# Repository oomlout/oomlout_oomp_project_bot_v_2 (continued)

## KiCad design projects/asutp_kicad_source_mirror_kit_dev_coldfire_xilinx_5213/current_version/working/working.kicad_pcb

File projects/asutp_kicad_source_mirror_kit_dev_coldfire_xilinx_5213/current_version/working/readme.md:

# kicad_source_mirror
 
## summary 
* id: asutp_kicad_source_mirror_kit_dev_coldfire_xilinx_5213
* user: asutp
* name: kicad_source_mirror
* board: kit_dev_coldfire_xilinx_5213
* repo: https://github.com/asutp/kicad-source-mirror
* src_file_repo_kicad_pcb: demos/kit-dev-coldfire-xilinx_5213/kit-dev-coldfire-xilinx_5213.kicad_pcb
* src_file_repo_kicad_pcb_link: https://github.com/asutp/kicad-source-mirror/tree/master/demos/kit-dev-coldfire-xilinx_5213/kit-dev-coldfire-xilinx_5213.kicad_pcb

* src_file_repo_sch: demos/interf_u/interf_u.sch
* src_file_repo_sch_link: https://github.com/asutp/kicad-source-mirror/tree/master/demos/interf_u/interf_u.sch
* full details link: https://github.com/oomlout/oomlout_oomp_project_bot_v_2/tree/main/projects/asutp_kicad_source_mirror_kit_dev_coldfire_xilinx_5213/current_version/working  

## pcb  

[board (pdf)](working.pdf)  

## working_bom
| Id | Designator | Footprint | Quantity | Designation | Supplier and ref |  | None | 
| --- | --- | --- | --- | --- | --- | --- | --- | 
| 1 | ABRT_SW1,RST_SW1,SW1,SW2 | SW_PUSH_SMALL | 4 | SW_PUSH |  |  | [''] | 
| 2 | ALLPST1,CLKOUT1,GND1,RS1,TA-1,VREF1 | PINTST | 6 | CONN_1 |  |  | [''] | 
| 3 | BDM_EN1,CAN_TERM1,CLK0,CLK1,CT1,LED_EN1,VDDA1,VX_EN1 | PIN_ARRAY_2X1 | 8 | JUMPER |  |  | [''] | 
| 4 | BDM_PORT1 | pin_array_13x2 | 1 | CONN_13X2 |  |  | [''] | 
| 5 | C1,C2 | SM0805 | 2 | 10pF |  |  | [''] | 
| 6 | C3,C20 | SM0805 | 2 | 1nF |  |  | [''] | 
| 7 | C4,C5,C7,C8,C9,C10,C14,C15,C18,C21,C22,C23,C24,C25,C26,C27,C28,C30,C31,C32,C33,C34,C35,C36,C41,C43,C44,C45,C46,C6,C11,C12,C51,C52,C53,C54,C55,C56,C57,C58,C59,C60,C61 | SM0805 | 43 | 100nF |  |  | [''] | 
| 8 | C16 | SM1206POL | 1 | 10uF |  |  | [''] | 
| 9 | C17 | SM1206POL | 1 | 100uF |  |  | [''] | 
| 10 | C38 | C2V8 | 1 | 10uF |  |  | [''] | 
| 11 | C40 | C2V8 | 1 | 220uF |  |  | [''] | 
| 12 | CAN_EN1,P3 | PIN_ARRAY_2X2 | 2 | CONN_2X2 |  |  | [''] | 
| 13 | COM_SEL1,COM_SEL2,COM_SEL3 | PIN_ARRAY_3X1 | 3 | CONN_3 |  |  | [''] | 
| 14 | D1,D3 | ST23AK#1 | 2 | BAT54 |  |  | [''] | 
| 15 | D7 | D5 | 1 | 1N4004 |  |  | [''] | 
| 16 | D8,D9,LED1,LED2,LED3,LED4,LED5 | SM1206POL | 7 | LED |  |  | [''] | 
| 17 | F1 | FSUPCMS | 1 | FUSE |  |  | [''] | 
| 18 | FB1 | SM1206 | 1 | BEAD |  |  | [''] | 
| 19 | J1 | JACK_ALIM | 1 | JACK_2P |  |  | [''] | 
| 20 | L1,L2 | SM1206 | 2 | 10uH |  |  | [''] | 
| 21 | LEDABRT1 | SM1206POL | 1 | RED |  |  | [''] | 
| 22 | LV1 | TO92-INVERT | 1 | DS1818 |  |  | [''] | 
| 23 | MCU_PORT1 | PIN_ARRAY_30X2 | 1 | CONN_30X2 |  |  | [''] | 
| 24 | P1 | PIN_ARRAY-6X1 | 1 | CONN_6 |  |  | [''] | 
| 25 | P4 | PIN_ARRAY_20X2 | 1 | CONN_20X2 |  |  | [''] | 
| 26 | PULUPEN1,UART_EN0,UART_EN1,UART_EN2 | pin_array_4x2 | 4 | CONN_4X2 |  |  | [''] | 
| 27 | Q1 | SOT23EBC | 1 | 3906 |  |  | [''] | 
| 28 | R1 | SM0805 | 1 | 1M |  |  | [''] | 
| 29 | R2,R15,R16,R17,R18,R19,R20,R21,R25,R45,R47,R48,R49,R50 | SM0805 | 14 | 4,7K |  |  | [''] | 
| 30 | R4,R5,R6,R8,R10,R11,R13,R23,R26,R30,R34,R35 | SM0805 | 12 | 10K |  |  | [''] | 
| 31 | R7,R36,R62,R63 | SM0805 | 4 | 1K |  |  | [''] | 
| 32 | R9 | SM0805 | 1 | 0 |  |  | [''] | 
| 33 | R12 | SM0805 | 1 | 20K |  |  | [''] | 
| 34 | R14,R22,R28,R31,R32,R33,R53 | SM0805 | 7 | 270 |  |  | [''] | 
| 35 | R38 | SM0805 | 1 | 62 |  |  | [''] | 
| 36 | R46 | SM0805 | 1 | 22 |  |  | [''] | 
| 37 | R57 | SM0805 | 1 | 4K7 |  |  | [''] | 
| 38 | R64 | R4 | 1 | 3,3 |  |  | [''] | 
| 39 | RCAN1,RCAN2 | SM0805 | 2 | R |  |  | [''] | 
| 40 | RED1 | SM1206POL | 1 | LED_RESET1 |  |  | [''] | 
| 41 | SW_ONOFF1 | SW_SPDT | 1 | SWITCH_INV |  |  | [''] | 
| 42 | TB1 | bornier2 | 1 | CONN_2 |  |  | [''] | 
| 43 | U1 | VQFP100 | 1 | MCF5213-LQFP100 |  |  | [''] | 
| 44 | U2 | SOT353 | 1 | 74AHC1G14 |  |  | [''] | 
| 45 | U3,U5,U8 | SO16E | 3 | MAX202 |  |  | [''] | 
| 46 | U4 | SO14E | 1 | 74HC125 |  |  | [''] | 
| 47 | U7 | SO8E | 1 | PCA82C251 |  |  | [''] | 
| 48 | U9 | TQFP144 | 1 | XCR3256-TQ144 |  |  | [''] | 
| 49 | UARTCAN0,UARTCAN1,UARTCAN2 | DB9FC | 3 | DB9 |  |  | [''] | 
| 50 | VR1 | DPAK5 | 1 | LT1129_QPACK |  |  | [''] | 
| 51 | Y1 | HC-18UH | 1 | 8MHz |  |  | [''] |

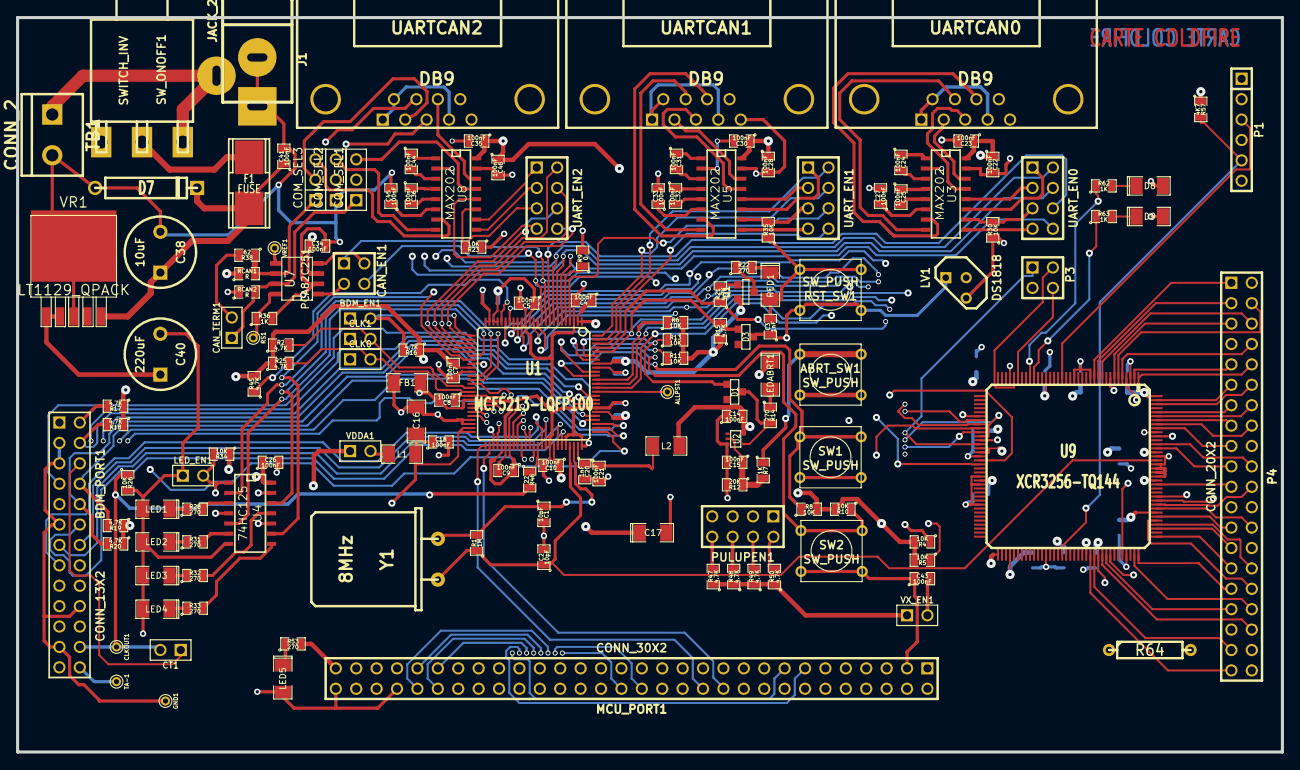
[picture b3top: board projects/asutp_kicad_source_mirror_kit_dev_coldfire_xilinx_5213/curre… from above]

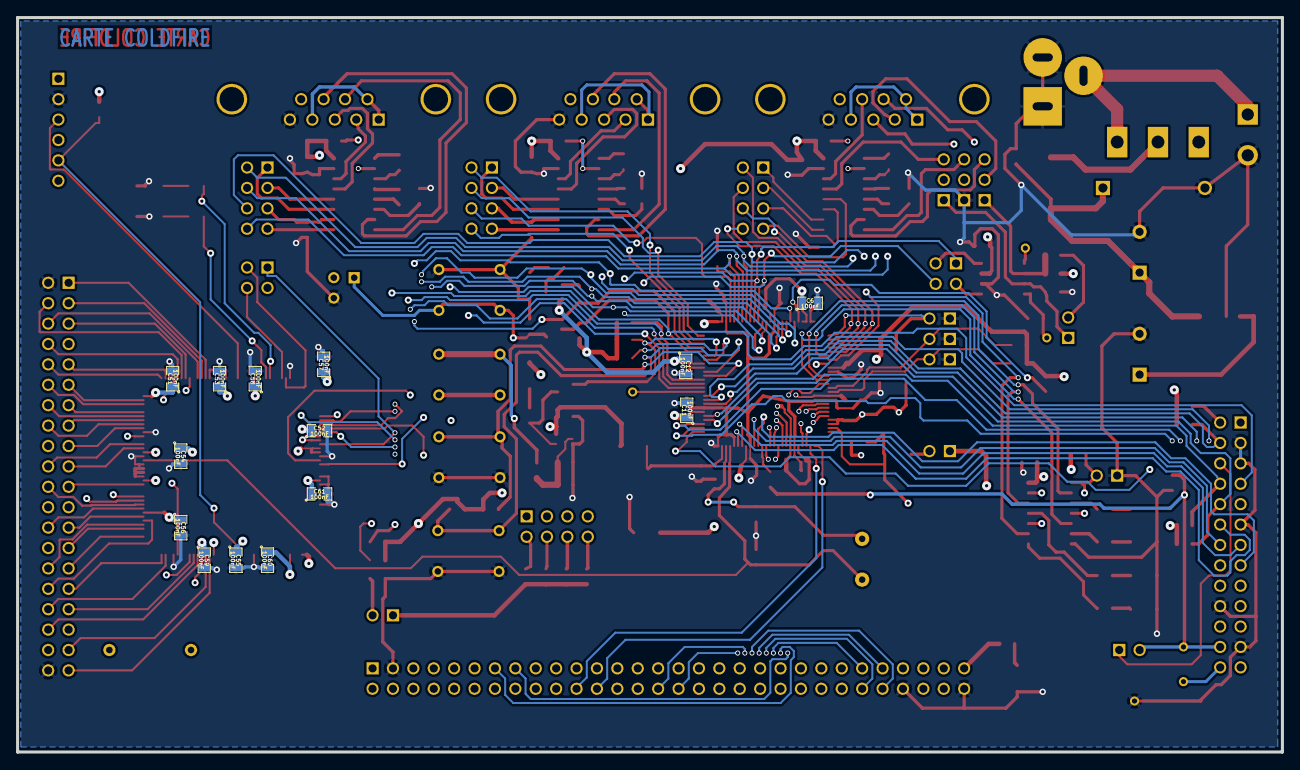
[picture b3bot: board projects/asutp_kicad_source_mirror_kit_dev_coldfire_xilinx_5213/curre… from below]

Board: 4 copper layers, 157.5 x 91.4 mm, 162 parts (14 on the bottom side), 209 nets.

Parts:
ABRT_SW1: SW_PUSH; SW_PUSH_SMALL
ALLPST1: CONN_1; PINTST
BDM_EN1: JUMPER; PIN_ARRAY_2X1
BDM_PORT1: CONN_13X2; pin_array_13x2
C1, C2: 10pF; SM0805
C3, C20: 1nF; SM0805
C4, C5, C6, C7, C8, C9, C10, C11, C12, C14, C15, C18, C21, C22, C23, C24, C25, C26, C27, C28, C30, C31, C32, C33, C34, C35, C36, C41, C43, C44, C45, C46, C51, C52, C53, C54, C55, C56, C57, C58, C59, C60, C61: 100nF; SM0805
C16: 10uF; SM1206POL
C17: 100uF; SM1206POL
C38: 10uF; C2V8
C40: 220uF; C2V8
CAN_EN1: CONN_2X2; PIN_ARRAY_2X2
CAN_TERM1: JUMPER; PIN_ARRAY_2X1
CLK0, CLK1: JUMPER; PIN_ARRAY_2X1
CLKOUT1: CONN_1; PINTST
COM_SEL1, COM_SEL2, COM_SEL3: CONN_3; PIN_ARRAY_3X1
CT1: JUMPER; PIN_ARRAY_2X1
D1, D3: BAT54; ST23AK#1
D7: 1N4004; D5
D8, D9: LED; SM1206POL
F1: FUSE; FSUPCMS
FB1: BEAD; SM1206
GND1: CONN_1; PINTST
J1: JACK_2P; JACK_ALIM
L1, L2: 10uH; SM1206
LED1, LED2, LED3, LED4, LED5: LED; SM1206POL
LEDABRT1: RED; SM1206POL
LED_EN1: JUMPER; PIN_ARRAY_2X1
LV1: DS1818; TO92-INVERT
MCU_PORT1: CONN_30X2; PIN_ARRAY_30X2
P1: CONN_6; PIN_ARRAY-6X1
P3: CONN_2X2; PIN_ARRAY_2X2
P4: CONN_20X2; PIN_ARRAY_20X2
PULUPEN1: CONN_4X2; pin_array_4x2
Q1: 3906; SOT23EBC
R1: 1M; SM0805
R2, R15, R16, R17, R18, R19, R20, R21, R25, R45, R47, R48, R49, R50: 4,7K; SM0805
R4, R5, R6, R8, R10, R11, R13, R23, R26, R30, R34, R35: 10K; SM0805
R7, R36, R62, R63: 1K; SM0805
R9: 0; SM0805
R12: 20K; SM0805
R14, R22, R28, R31, R32, R33, R53: 270; SM0805
R38: 62; SM0805
R46: 22; SM0805
R57: 4K7; SM0805
R64: 3,3; R4
RCAN1, RCAN2: R; SM0805
RED1: LED_RESET1; SM1206POL
RS1: CONN_1; PINTST
RST_SW1: SW_PUSH; SW_PUSH_SMALL
SW1, SW2: SW_PUSH; SW_PUSH_SMALL
SW_ONOFF1: SWITCH_INV; SW_SPDT
TA-1: CONN_1; PINTST
TB1: CONN_2; bornier2
U1: MCF5213-LQFP100; VQFP100
U2: 74AHC1G14; SOT353
U3, U5, U8: MAX202; SO16E
U4: 74HC125; SO14E
U7: PCA82C251; SO8E
U9: XCR3256-TQ144; TQFP144
UARTCAN0, UARTCAN1, UARTCAN2: DB9; DB9FC
UART_EN0, UART_EN1, UART_EN2: CONN_4X2; pin_array_4x2
VDDA1: JUMPER; PIN_ARRAY_2X1
VR1: LT1129_QPACK; DPAK5
VREF1: CONN_1; PINTST
VX_EN1: JUMPER; PIN_ARRAY_2X1
Y1: 8MHz; HC-18UH

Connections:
/ALLPST: ALLPST1.1, U1.86
/AN0: MCU_PORT1.10, U1.43
/AN1: MCU_PORT1.12, U1.44
/AN2: MCU_PORT1.14, U1.45
/AN3: MCU_PORT1.16, U1.46
/AN4: MCU_PORT1.18, U1.54
/AN5: MCU_PORT1.20, U1.53
/AN6: MCU_PORT1.22, U1.52
/AN7: MCU_PORT1.24, U1.51
/BKPT-: BDM_PORT1.2, R17.2, U1.76
/CLKIN/EXTAL: C1.1, R1.2, U1.73, Y1.1
/CLKMOD0: CLK0.2, R25.2, U1.40
/CLKMOD1: CLK1.2, R2.2, U1.39
/DDAT0: BDM_PORT1.19, U1.77
/DDAT1: BDM_PORT1.18, U1.78
/DDAT2: BDM_PORT1.17, U1.83
/DDAT3: BDM_PORT1.16, U1.84
/DSCLK: BDM_PORT1.4, R18.2, U1.85
/DSI: BDM_PORT1.8, R19.2, U1.79
/DSO: BDM_PORT1.10, R20.2, U1.80
/DTIN0: MCU_PORT1.34, U1.36, U4.2
/DTIN1: MCU_PORT1.36, U1.37, U4.5
/DTIN2: MCU_PORT1.38, U1.31, U4.12
/DTIN3: MCU_PORT1.40, U1.32, U4.9
/GPT0: MCU_PORT1.49, U1.58
/GPT1: MCU_PORT1.50, U1.59
/GPT2: MCU_PORT1.51, U1.61
/GPT3: MCU_PORT1.52, U1.62
/IRQ-4: MCU_PORT1.33, R8.1, SW1.1, U1.90
/IRQ-5: MCU_PORT1.35, R10.1, SW2.1, U1.91
/IRQ-6: MCU_PORT1.37, R11.1, U1.94
/IRQ-7: D1.1, MCU_PORT1.39, R13.1, U1.95
/JTAG_EN: BDM_EN1.2, R16.2, U1.26
/PST0: BDM_PORT1.15, U1.65
/PST1: BDM_PORT1.14, U1.66
/PST2: BDM_PORT1.13, U1.69
/PST3: BDM_PORT1.12, U1.70
/QSPI_CS0: MCU_PORT1.23, PULUPEN1.3, U1.20
/QSPI_CS3: MCU_PORT1.29, U1.12
/TCLK: BDM_PORT1.24, CLKOUT1.1, CT1.2, R26.1, R46.2
/VDDPLL: C20.1, C21.1, L2.2, U1.74
/inout_user/CANRX: CAN_EN1.4, MCU_PORT1.28, PULUPEN1.7, U1.11
/inout_user/CANTX: CAN_EN1.1, MCU_PORT1.26, PULUPEN1.5, U1.10
/inout_user/CAN_H: CAN_TERM1.1, COM_SEL1.1, RCAN2.2, U7.7
/inout_user/CAN_L: COM_SEL3.1, R38.1, RCAN1.2, U7.6
/inout_user/CTS0: U3.8, UARTCAN0.7
/inout_user/CTS1: U5.8, UARTCAN1.7
/inout_user/CTS2/CANH: COM_SEL1.2, UARTCAN2.7
/inout_user/PWM1: MCU_PORT1.13, U1.38
/inout_user/PWM3: MCU_PORT1.15, U1.33
/inout_user/PWM5: MCU_PORT1.30, U1.60
/inout_user/PWM7: MCU_PORT1.32, U1.63
/inout_user/QSPI_DIN: MCU_PORT1.19, U1.16, U9.46
/inout_user/QSPI_DOUT: MCU_PORT1.17, U1.17, U9.47
/inout_user/QSPI_SCLK: MCU_PORT1.21, PULUPEN1.1, U1.18, U9.48
/inout_user/RCON-: MCU_PORT1.53, R45.1, U1.21
/inout_user/RSTI-: BDM_PORT1.7, D3.1, MCU_PORT1.6, R15.2, U1.96
/inout_user/RTS0: U3.7, UARTCAN0.8
/inout_user/RTS0-: MCU_PORT1.4, R21.1, U1.97
/inout_user/RTS1: U5.7, UARTCAN1.8
/inout_user/RTS2: U8.14, UARTCAN2.8
/inout_user/RXD0: U3.13, UARTCAN0.3
/inout_user/RXD1: U5.13, UARTCAN1.3
/inout_user/RXD2: COM_SEL2.2, UARTCAN2.3
/inout_user/RxD_CAN: CAN_EN1.2, U7.4
/inout_user/TXD0: U3.14, UARTCAN0.2
/inout_user/TXD1: U5.14, UARTCAN1.2
/inout_user/TXD2/CANL: COM_SEL3.2, UARTCAN2.2
/inout_user/TxD_CAN: CAN_EN1.3, U7.1
/inout_user/UCTS0: MCU_PORT1.44, U1.6, UART_EN0.8
/inout_user/UCTS1: MCU_PORT1.11, P3.1, U1.98, U9.49, UART_EN1.8
/inout_user/UCTS2: MCU_PORT1.48, U1.27, UART_EN2.8
/inout_user/URTS0: MCU_PORT1.42, U1.9, UART_EN0.6
/inout_user/URTS1: MCU_PORT1.9, P3.3, U1.4, U9.53, UART_EN1.6
/inout_user/URTS2: MCU_PORT1.46, U1.30, UART_EN2.6
/inout_user/URXD0: MCU_PORT1.43, U1.7, UART_EN0.4
/inout_user/URXD1: MCU_PORT1.7, U1.100, UART_EN1.4
/inout_user/URXD2: MCU_PORT1.47, U1.28, UART_EN2.4
/inout_user/UTXD0: MCU_PORT1.41, U1.8, UART_EN0.2
/inout_user/UTXD1: MCU_PORT1.5, U1.99, UART_EN1.2
/inout_user/UTXD2: MCU_PORT1.45, U1.29, UART_EN2.2
/inout_user/VCCA: C16.1, C18.1, L1.2, MCU_PORT1.55, MCU_PORT1.57, U1.49, U1.50
/xilinx/+3,3V_OUT: P4.38, R64.2
/xilinx/GLCK2: C2.1, R1.1, U1.72, U9.128, Y1.2
/xilinx/IRQ-1: MCU_PORT1.2, R4.1, U1.87, U9.42
/xilinx/IRQ-2: MCU_PORT1.8, R5.1, U1.88, U9.43
/xilinx/IRQ-3: MCU_PORT1.31, R6.1, U1.89, U9.44
/xilinx/LED_TEST1: R62.1, U9.28
/xilinx/LED_TEST2: R63.1, U9.27
/xilinx/QSPI_CS1: MCU_PORT1.25, U1.19, U9.54
/xilinx/QSPI_CS2: MCU_PORT1.27, U1.13, U9.45
/xilinx/TCK: P1.5, R57.2, U9.89
/xilinx/TDI: P1.4, U9.4
/xilinx/TDO: P1.6, U9.104
/xilinx/TMS: P1.3, U9.20
/xilinx/XIL_D0: P4.1, U9.12
/xilinx/XIL_D1: P4.3, U9.11
/xilinx/XIL_D2: P4.5, U9.7
/xilinx/XIL_D3: P4.7, U9.8
/xilinx/XIL_D4: P4.9, U9.2
/xilinx/XIL_D5: P4.11, U9.143
/xilinx/XIL_D6: P4.13, U9.140
/xilinx/XIL_D7: P4.15, U9.138
/xilinx/XIL_D8: P4.17, U9.136
/xilinx/XIL_D9: P4.19, U9.131
/xilinx/XIL_D10: P4.21, U9.122
/xilinx/XIL_D11: P4.23, U9.119
/xilinx/XIL_D12: P4.25, U9.114
/xilinx/XIL_D13: P4.27, U9.111
/xilinx/XIL_D14: P4.29, U9.109
/xilinx/XIL_D15: P4.31, U9.108
/xilinx/XIL_D16: P4.33, U9.100
/xilinx/XIL_D17: P4.35, U9.101
/xilinx/XIL_D18: P4.37, U9.97
/xilinx/XIL_D19: P4.39, U9.96
/xilinx/XIL_D20: P4.4, U9.6
/xilinx/XIL_D21: P4.6, U9.10
/xilinx/XIL_D22: P4.8, U9.5
/xilinx/XIL_D23: P4.10, U9.1
/xilinx/XIL_D24: P4.12, U9.142
/xilinx/XIL_D25: P4.14, U9.139
/xilinx/XIL_D26: P4.16, U9.137
/xilinx/XIL_D27: P4.18, U9.134
/xilinx/XIL_D28: P4.20, U9.132
/xilinx/XIL_D29: P4.22, U9.117
/xilinx/XIL_D30: P4.24, U9.118
/xilinx/XIL_D31: P4.26, U9.116
/xilinx/XIL_D32: P4.28, U9.98
/xilinx/XIL_D33: P4.30, U9.112
/xilinx/XIL_D34: P4.32, U9.113
/xilinx/XIL_D35: P4.34, U9.107
/xilinx/XIL_D36: P4.36, U9.99
GND: BDM_EN1.1, BDM_PORT1.3, BDM_PORT1.5, BDM_PORT1.11, BDM_PORT1.20, BDM_PORT1.23, C1.2, C2.2, C3.2, C4.2, C5.2, C6.2, C7.2, C8.2, C9.2, C10.2, C11.2, C12.2, C14.1, C15.2, C17.2, C20.2, C21.2, C22.2, C26.2, C27.2, C28.2, C33.2, C34.2, C38.2, C40.2, C41.2, C43.1, C45.2, C46.2, C51.2, C52.2, C53.2, C54.2, C55.2, C56.2, C57.2, C58.2, C59.2, C60.2, C61.2, CLK0.1, CLK1.1, COM_SEL2.1, D7.1, D8.2, D9.2, FB1.1, GND1.1, J1.1, J1.2, LED1.2, LED2.2, LED3.2, LED4.2, LED5.2, LED_EN1.1, LV1.3, MCU_PORT1.3, MCU_PORT1.54, MCU_PORT1.60, P1.2, P4.2, P4.40, R9.2, R12.2, R23.1, R26.2, R30.1, R35.1, R36.2, RCAN2.1, RED1.2, RST_SW1.2, SW1.2, SW2.2, TB1.2, U1.3, U1.15, U1.24, U1.25, U1.35, U1.42, U1.56, U1.67, U1.71, U1.75, U1.82, U1.92, U2.3, U3.15, U4.7, U5.15, U7.2, U8.15, U9.3, U9.13, U9.17, U9.33, U9.52, U9.57, U9.59, U9.64, U9.85, U9.105, U9.124, U9.125, U9.126, U9.127, U9.129, U9.135, UARTCAN0.5, UARTCAN1.5, UARTCAN2.5, VR1.3
GNDA: C16.2, C18.2, FB1.2, MCU_PORT1.56, MCU_PORT1.58, U1.47, U1.48
unnamed: ABRT_SW1.1, R7.1
unnamed: BDM_PORT1.6, CT1.1
unnamed: BDM_PORT1.26, TA-1.1
unnamed: C3.1, D3.2, LV1.1, RST_SW1.1
unnamed: C15.1, R7.2, R12.1, U2.2
unnamed: C23.2, U3.2
unnamed: C24.1, U3.1
unnamed: C24.2, U3.3
unnamed: C25.1, U3.4
unnamed: C25.2, U3.5
unnamed: C27.1, U3.6
unnamed: C30.2, U5.2
unnamed: C31.1, U5.1
unnamed: C31.2, U5.3
unnamed: C32.1, U5.4
unnamed: C32.2, U5.5
unnamed: C33.1, U5.6
unnamed: C35.2, U8.2
unnamed: C36.1, U8.4
unnamed: C36.2, U8.5
unnamed: C38.1, C41.1, D7.2, F1.2, VR1.5
unnamed: C43.2, MCU_PORT1.1, VX_EN1.2
unnamed: C44.1, U8.1
unnamed: C44.2, U8.3
unnamed: C45.1, U8.6
unnamed: CAN_TERM1.2, R38.2
unnamed: COM_SEL1.3, U8.13
unnamed: COM_SEL2.3, U8.8
unnamed: COM_SEL3.3, U8.7
unnamed: D1.2, R14.2, U2.4
unnamed: D8.1, R62.2
unnamed: D9.1, R63.2
unnamed: F1.1, SW_ONOFF1.2
unnamed: J1.3, SW_ONOFF1.3, TB1.1
unnamed: L1.1, VDDA1.2
unnamed: LED1.1, R28.1
unnamed: LED2.1, R31.1
unnamed: LED3.1, R32.1
unnamed: LED4.1, R33.1
unnamed: LED5.1, R53.1
unnamed: LEDABRT1.2, R14.1
unnamed: LED_EN1.2, R34.2, U4.1, U4.4, U4.10, U4.13
unnamed: P3.2, U9.32
unnamed: P3.4, U9.31
unnamed: PULUPEN1.2, R50.2
unnamed: PULUPEN1.4, R49.2
unnamed: PULUPEN1.6, R48.2
unnamed: PULUPEN1.8, R47.2
unnamed: Q1.2, R21.2
unnamed: Q1.3, R22.1
unnamed: R9.1, U1.5
unnamed: R22.2, RED1.1
unnamed: R23.2, U8.11, UART_EN2.5
unnamed: R28.2, U4.3
unnamed: R30.2, U3.10, UART_EN0.5
unnamed: R31.2, U4.6
unnamed: R32.2, U4.11
unnamed: R33.2, U4.8
unnamed: R35.2, U5.10, UART_EN1.5
unnamed: R36.1, RS1.1, U7.8
unnamed: R46.1, U1.64
unnamed: U3.9, UART_EN0.7
unnamed: U3.11, UART_EN0.1
unnamed: U3.12, UART_EN0.3
unnamed: U5.9, UART_EN1.7
unnamed: U5.11, UART_EN1.1
unnamed: U5.12, UART_EN1.3
unnamed: U7.5, VREF1.1
unnamed: U8.9, UART_EN2.3
unnamed: U8.10, UART_EN2.1
unnamed: U8.12, UART_EN2.7
unnamed: UARTCAN0.1, UARTCAN0.4, UARTCAN0.6
unnamed: UARTCAN1.1, UARTCAN1.4, UARTCAN1.6
unnamed: UARTCAN2.1, UARTCAN2.4, UARTCAN2.6
VDD: ABRT_SW1.2, BDM_PORT1.9, BDM_PORT1.25, C4.1, C5.1, C6.1, C7.1, C8.1, C9.1, C10.1, C11.1, C12.1, C14.2, C17.1, C22.1, C23.1, C26.1, C28.1, C30.1, C34.1, C35.1, C40.1, C46.1, C51.1, C52.1, C53.1, C54.1, C55.1, C56.1, C57.1, C58.1, C59.1, C60.1, C61.1, L2.1, LEDABRT1.1, LV1.2, MCU_PORT1.59, P1.1, Q1.1, R2.1, R4.2, R5.2, R6.2, R8.2, R10.2, R11.2, R13.2, R15.1, R16.1, R17.1, R18.1, R19.1, R20.1, R25.1, R34.1, R45.2, R47.1, R48.1, R49.1, R50.1, R53.2, R57.1, R64.1, RCAN1.1, U1.1, U1.2, U1.14, U1.22, U1.23, U1.34, U1.41, U1.55, U1.57, U1.68, U1.81, U1.93, U2.5, U3.16, U4.14, U5.16, U7.3, U8.16, U9.24, U9.50, U9.51, U9.58, U9.73, U9.76, U9.95, U9.115, U9.123, U9.130, U9.144, VDDA1.1, VR1.1, VR1.2, VX_EN1.1

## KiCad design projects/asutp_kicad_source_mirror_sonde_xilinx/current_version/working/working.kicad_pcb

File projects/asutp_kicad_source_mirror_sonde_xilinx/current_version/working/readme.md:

# kicad_source_mirror
 
## summary 
* id: asutp_kicad_source_mirror_sonde_xilinx
* user: asutp
* name: kicad_source_mirror
* board: sonde_xilinx
* repo: https://github.com/asutp/kicad-source-mirror
* src_file_repo_kicad_pcb: demos/sonde xilinx/sonde xilinx.kicad_pcb
* src_file_repo_kicad_pcb_link: https://github.com/asutp/kicad-source-mirror/tree/master/demos/sonde xilinx/sonde xilinx.kicad_pcb

* src_file_repo_sch: demos/sonde xilinx/sonde xilinx.sch
* src_file_repo_sch_link: https://github.com/asutp/kicad-source-mirror/tree/master/demos/sonde xilinx/sonde xilinx.sch
* full details link: https://github.com/oomlout/oomlout_oomp_project_bot_v_2/tree/main/projects/asutp_kicad_source_mirror_sonde_xilinx/current_version/working  

## schematic  
  
[schematic (pdf)](working_schematic.pdf) 

## pcb  

[board (pdf)](working.pdf)  

## working_bom
| Id | Designator | Footprint | Quantity | Designation | Supplier and ref |  | None | 
| --- | --- | --- | --- | --- | --- | --- | --- | 
| 1 | U1,U2 | 14DIP-ELL300 | 2 | 74LS125 |  |  | [''] | 
| 2 | R13,R7,R14,R10,R1,R9,R6,R8,R11,R12 | R4 | 10 | 100 |  |  | [''] | 
| 3 | D1,D2 | D3 | 2 | BAT46 |  |  | [''] | 
| 4 | C1 | CP5 | 1 | 1uF |  |  | [''] | 
| 5 | R4 | R4 | 1 | 47 |  |  | [''] | 
| 6 | C5,C3,C2,C4 | C2 | 4 | 100pF |  |  | [''] | 
| 7 | P1 | bornier6 | 1 | CONN_6 |  |  | [''] | 
| 8 | R5 | R4 | 1 | 1K |  |  | [''] | 
| 9 | R2 | R4 | 1 | 5,1K |  |  | [''] | 
| 10 | J2 | DB9M_CI_INVERT | 1 | DB9MALE |  |  | [''] | 
| 11 | J1 | DB25M_CI | 1 | DB25MALE |  |  | [''] | 

## bom_schematic
| Ref | Qnty | Value | Cmp name | Footprint | Description | Vendor | DNP | 
| --- | --- | --- | --- | --- | --- | --- | --- | 
| C1 | 1 | 1uF | CP | Discret:CP5 |  |  |  | 
| C2, C3, C4, C5 | 4 | 100pF | C | Discret:C2 |  |  |  | 
| D1, D2 | 2 | BAT46 | DIODESCH | Discret:D3 |  |  |  | 
| J1 | 1 | DB25MALE | DB25 | Connect:DB25M_CI |  |  |  | 
| J2 | 1 | DB9MALE | DB9 | Connect:DB9M_CI_INVERT |  |  |  | 
| P1 | 1 | CONN_6 | CONN_6 | Connect:bornier6 |  |  |  | 
| R1, R6, R7, R8, R9, R10, R11, R12, R13, R14 | 10 | 100 | R | Discret:R4 |  |  |  | 
| R2 | 1 | 5,1K | R | Discret:R4 |  |  |  | 
| R4 | 1 | 47 | R | Discret:R4 |  |  |  | 
| R5 | 1 | 1K | R | Discret:R4 |  |  |  | 
| U1, U2 | 2 | 74LS125 | 74LS125 | Sockets_DIP:DIP-14__300_ELL |  |  |  |

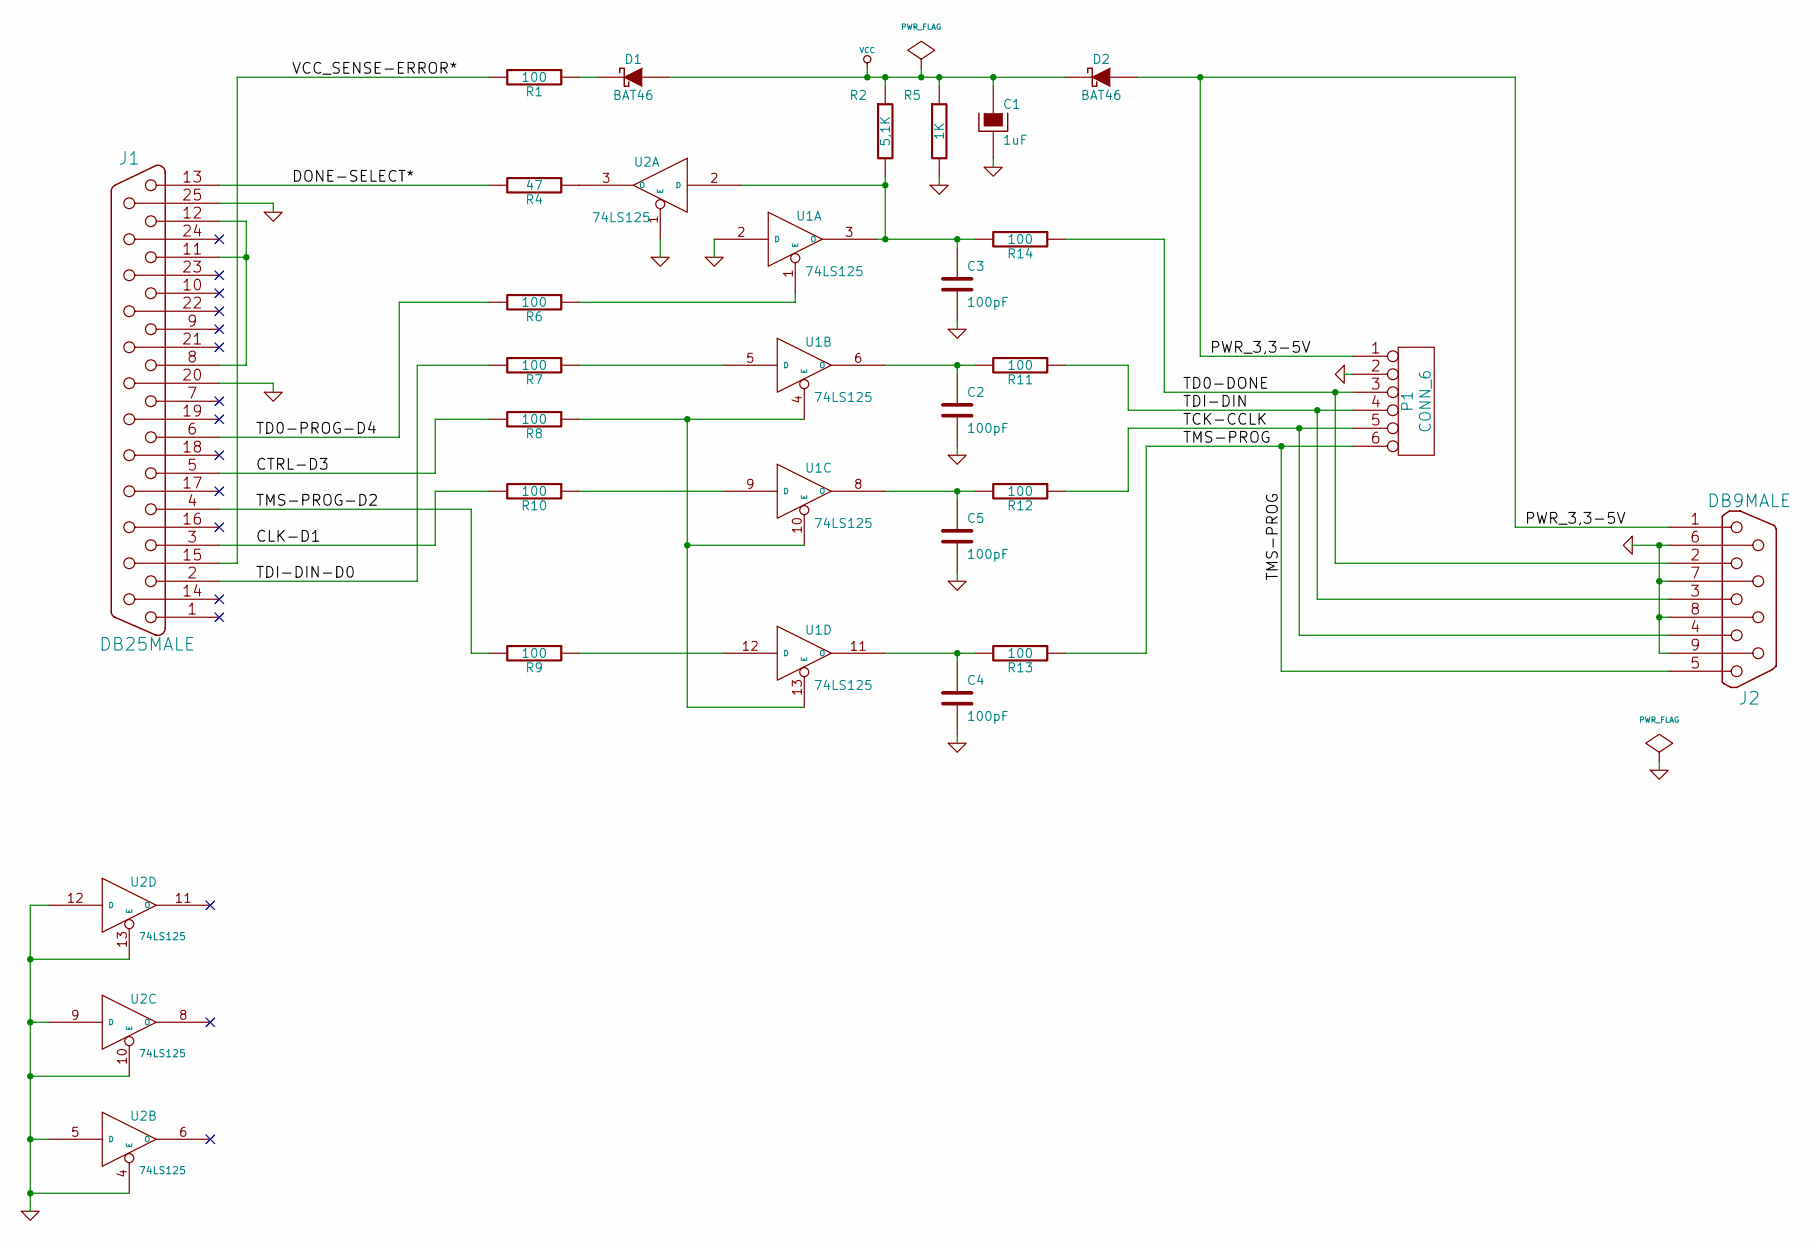
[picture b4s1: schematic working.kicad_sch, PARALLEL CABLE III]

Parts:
C1: 1uF; CP5
C2, C3, C4, C5: 100pF; C2
D1, D2: BAT46; D3
J1: DB25MALE; DB25M_CI
J2: DB9MALE; DB9M_CI_INVERT
P1: CONN_6; bornier6
R1, R6, R7, R8, R9, R10, R11, R12, R13, R14: 100; R4
R2: 5,1K; R4
R4: 47; R4
R5: 1K; R4
U1, U2: 74LS125; DIP-14__300_ELL

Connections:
/CLK-D1: J1.3, R10.2
/CTRL-D3: J1.5, R8.2
/DONE-SELECT*: J1.13, R4.2
/PWR_3,3-5V: D2.1 (A), J2.1, P1.1
/TCK-CCLK: J2.4, P1.5, R12.1
/TD0-DONE: J2.2, P1.3, R14.1
/TD0-PROG-D4: J1.6, R6.2
/TDI-DIN: J2.3, P1.4, R11.1
/TDI-DIN-D0: J1.2, R7.2
/TMS-PROG: J2.5, P1.6, R13.1
/TMS-PROG-D2: J1.4, R9.2
/VCC_SENSE-ERROR*: J1.15, R1.2
GND: C1.2, C2.2, C3.2, C4.2, C5.2, J1.20, J1.25, J2.6, J2.7, J2.8, J2.9, P1.2, R5.2, U1.2 (D), U1.7 (GND), U2.1 (E), U2.4 (E), U2.5 (D), U2.7 (GND), U2.9 (D), U2.10 (E), U2.12 (D), U2.13 (E)
unnamed: J1.8, J1.11, J1.12
unnamed: D1.2 (K), R1.1
unnamed: R4.1, U2.3 (O)
unnamed: R7.1, U1.5 (D)
unnamed: R10.1, U1.9 (D)
unnamed: R6.1, U1.1 (E)
unnamed: R9.1, U1.12 (D)
unnamed: R8.1, U1.4 (E), U1.10 (E), U1.13 (E)
unnamed: C4.1, R13.2, U1.11 (O)
unnamed: C2.1, R11.2, U1.6 (O)
unnamed: C5.1, R12.2, U1.8 (O)
unnamed: C3.1, R2.2, R14.2, U1.3 (O), U2.2 (D)
VCC: C1.1, D1.1 (A), D2.2 (K), R2.1, R5.1, U1.14 (VCC), U2.14 (VCC)

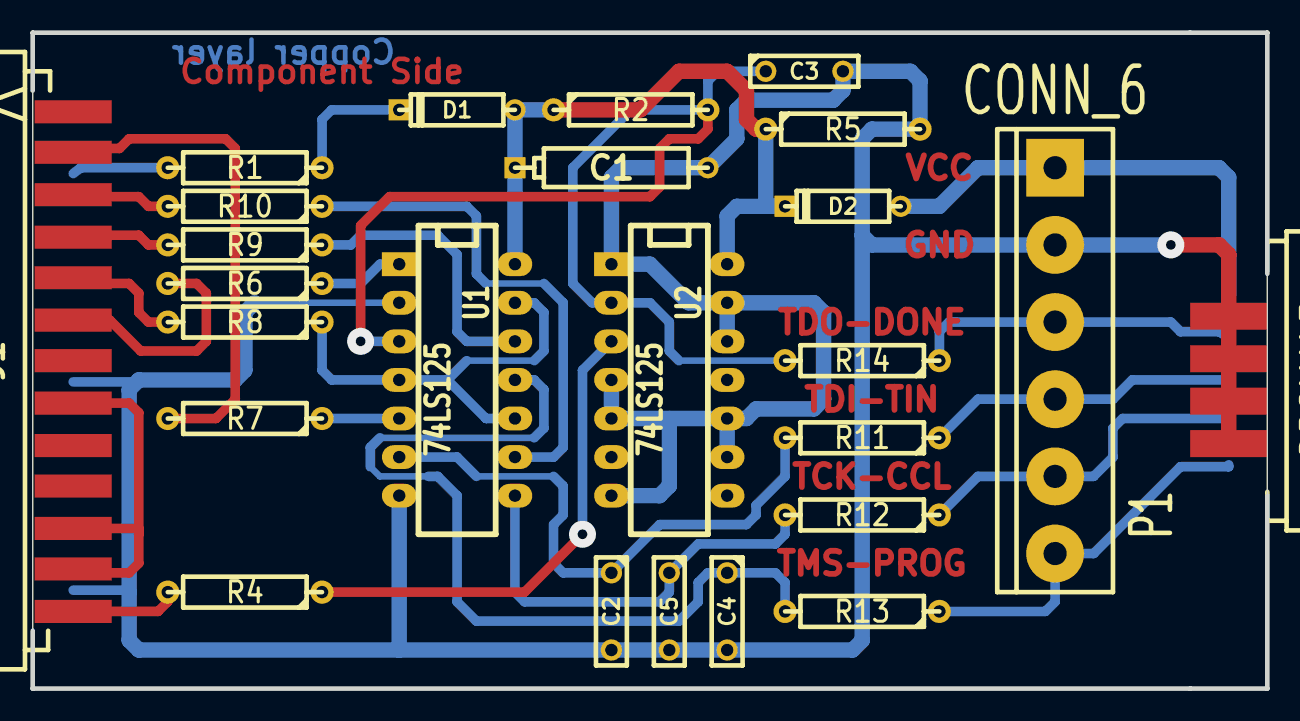
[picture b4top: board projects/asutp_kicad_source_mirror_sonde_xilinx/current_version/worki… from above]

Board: 2 copper layers, 81.3 x 43.2 mm, 25 parts (0 on the bottom side), 26 nets.

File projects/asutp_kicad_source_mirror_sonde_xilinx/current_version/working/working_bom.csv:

"Id";"Designator";"Footprint";"Quantity";"Designation";"Supplier and ref";
1;"U1,U2";"14DIP-ELL300";2;"74LS125";;;
2;"R13,R7,R14,R10,R1,R9,R6,R8,R11,R12";"R4";10;"100";;;
3;"D1,D2";"D3";2;"BAT46";;;
4;"C1";"CP5";1;"1uF";;;
5;"R4";"R4";1;"47";;;
6;"C5,C3,C2,C4";"C2";4;"100pF";;;
7;"P1";"bornier6";1;"CONN_6";;;
8;"R5";"R4";1;"1K";;;
9;"R2";"R4";1;"5,1K";;;
10;"J2";"DB9M_CI_INVERT";1;"DB9MALE";;;
11;"J1";"DB25M_CI";1;"DB25MALE";;;
